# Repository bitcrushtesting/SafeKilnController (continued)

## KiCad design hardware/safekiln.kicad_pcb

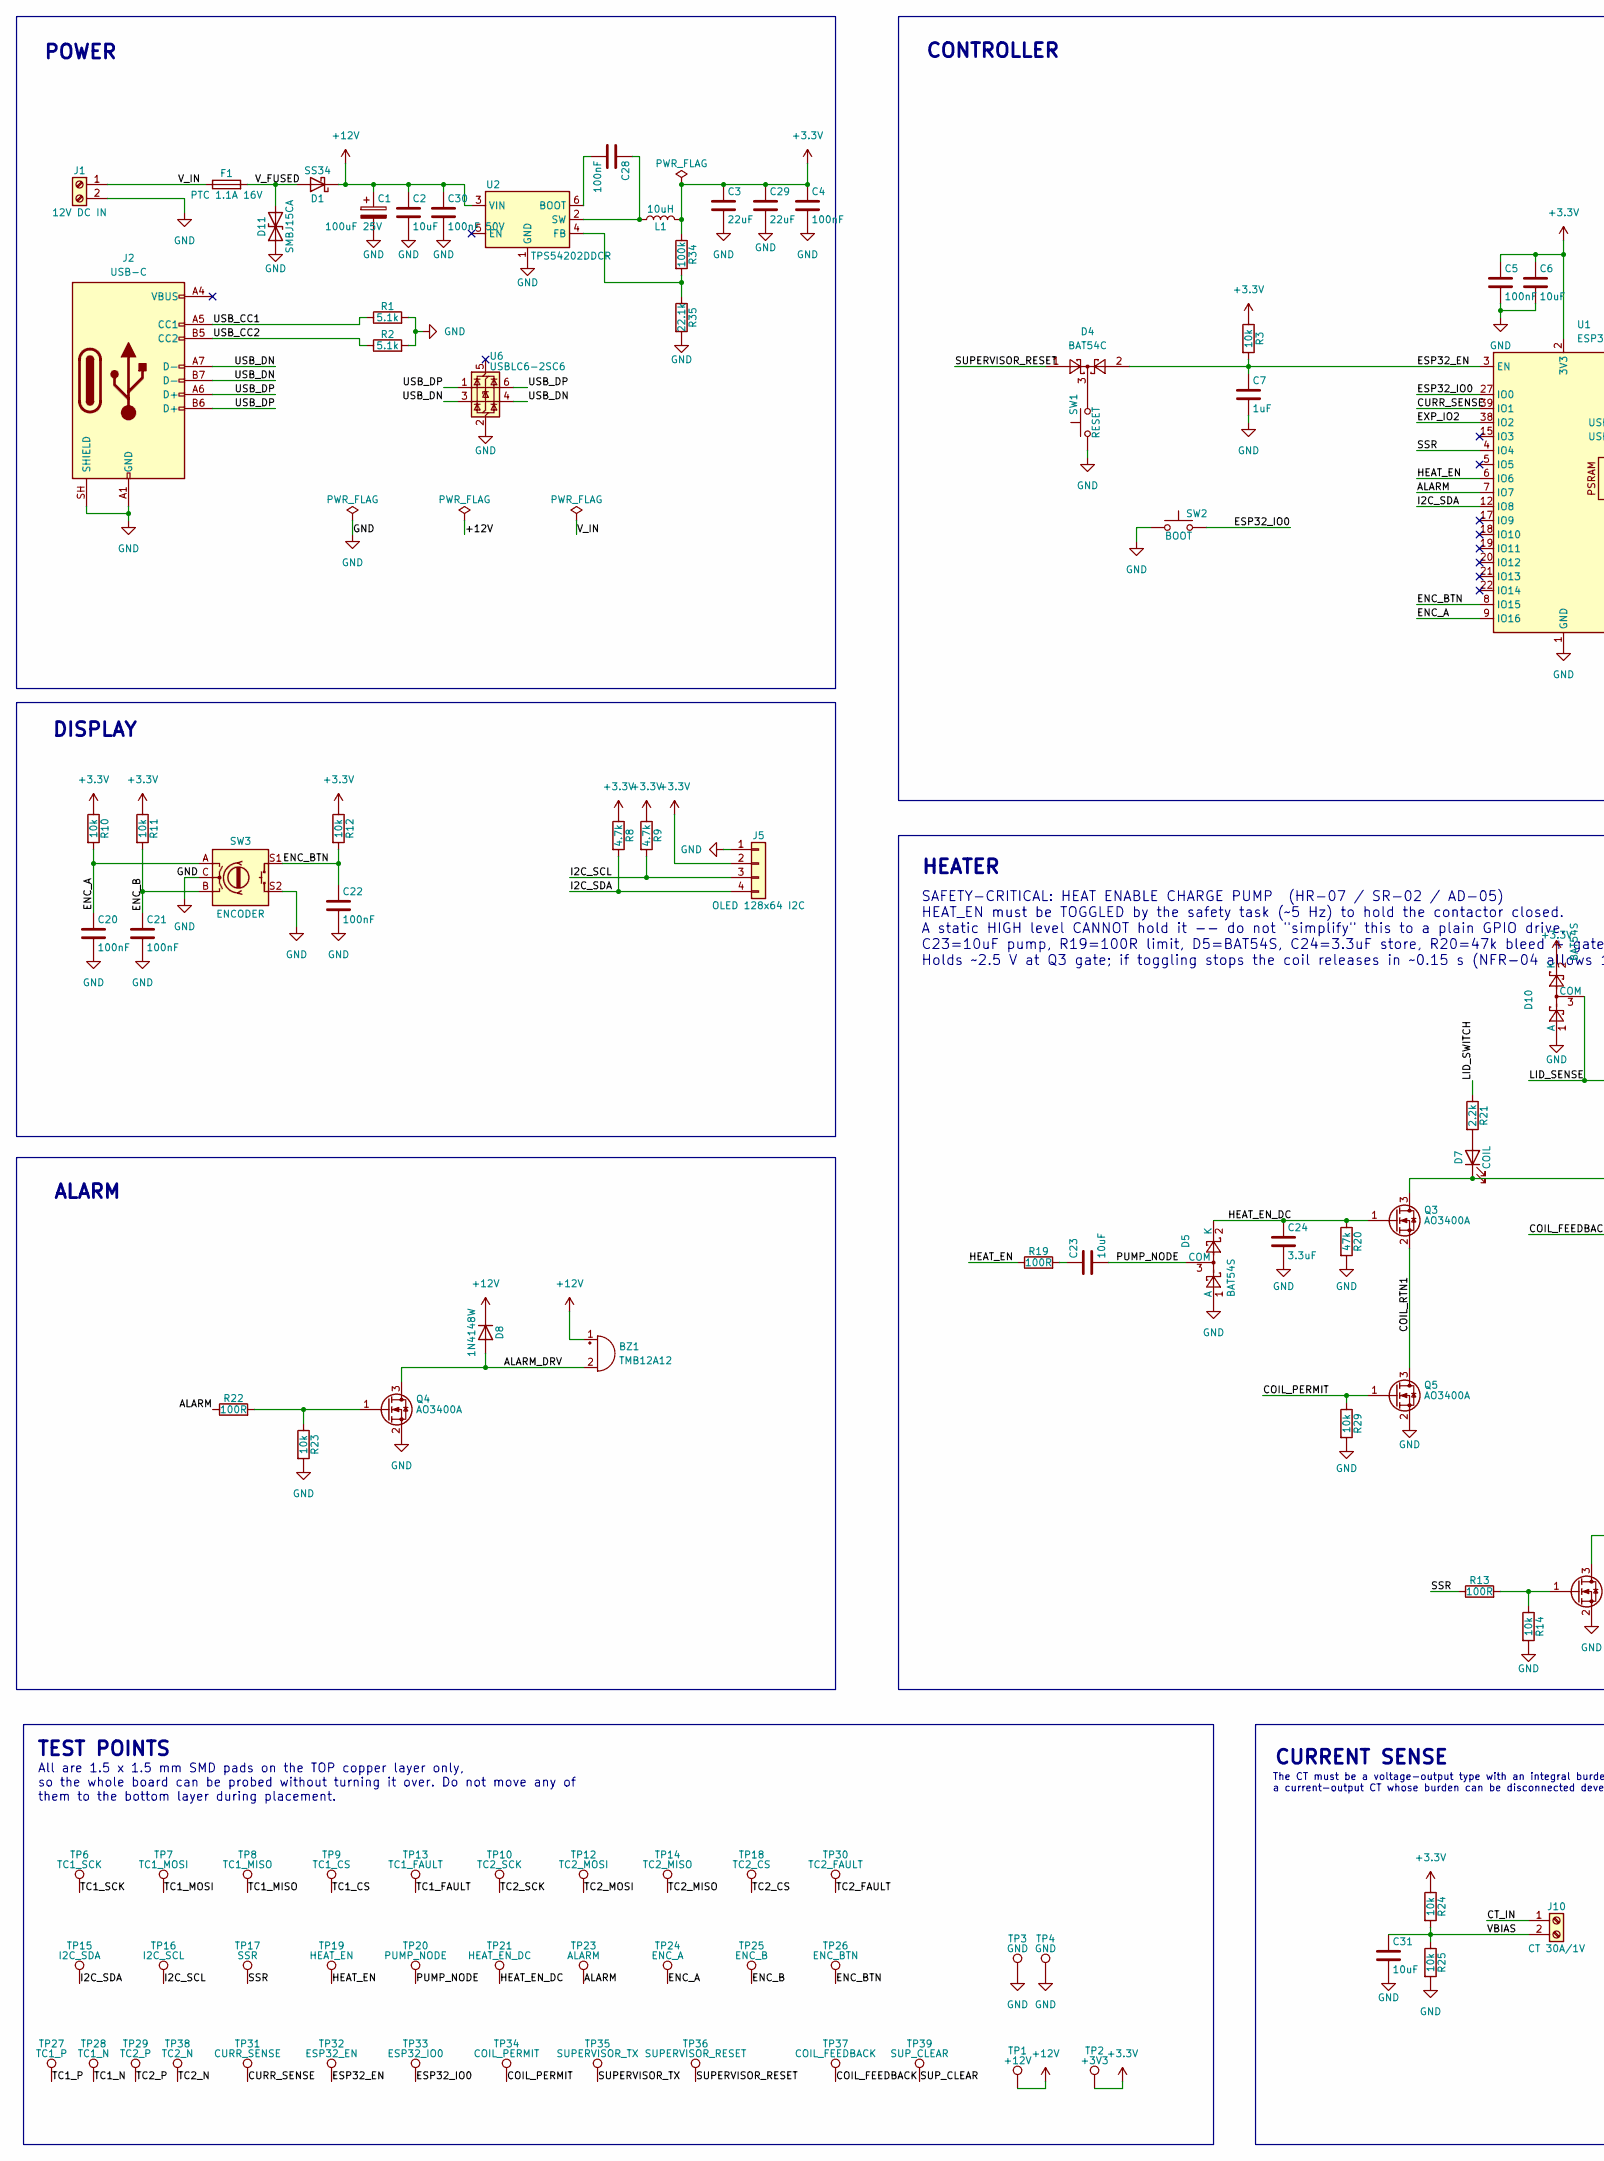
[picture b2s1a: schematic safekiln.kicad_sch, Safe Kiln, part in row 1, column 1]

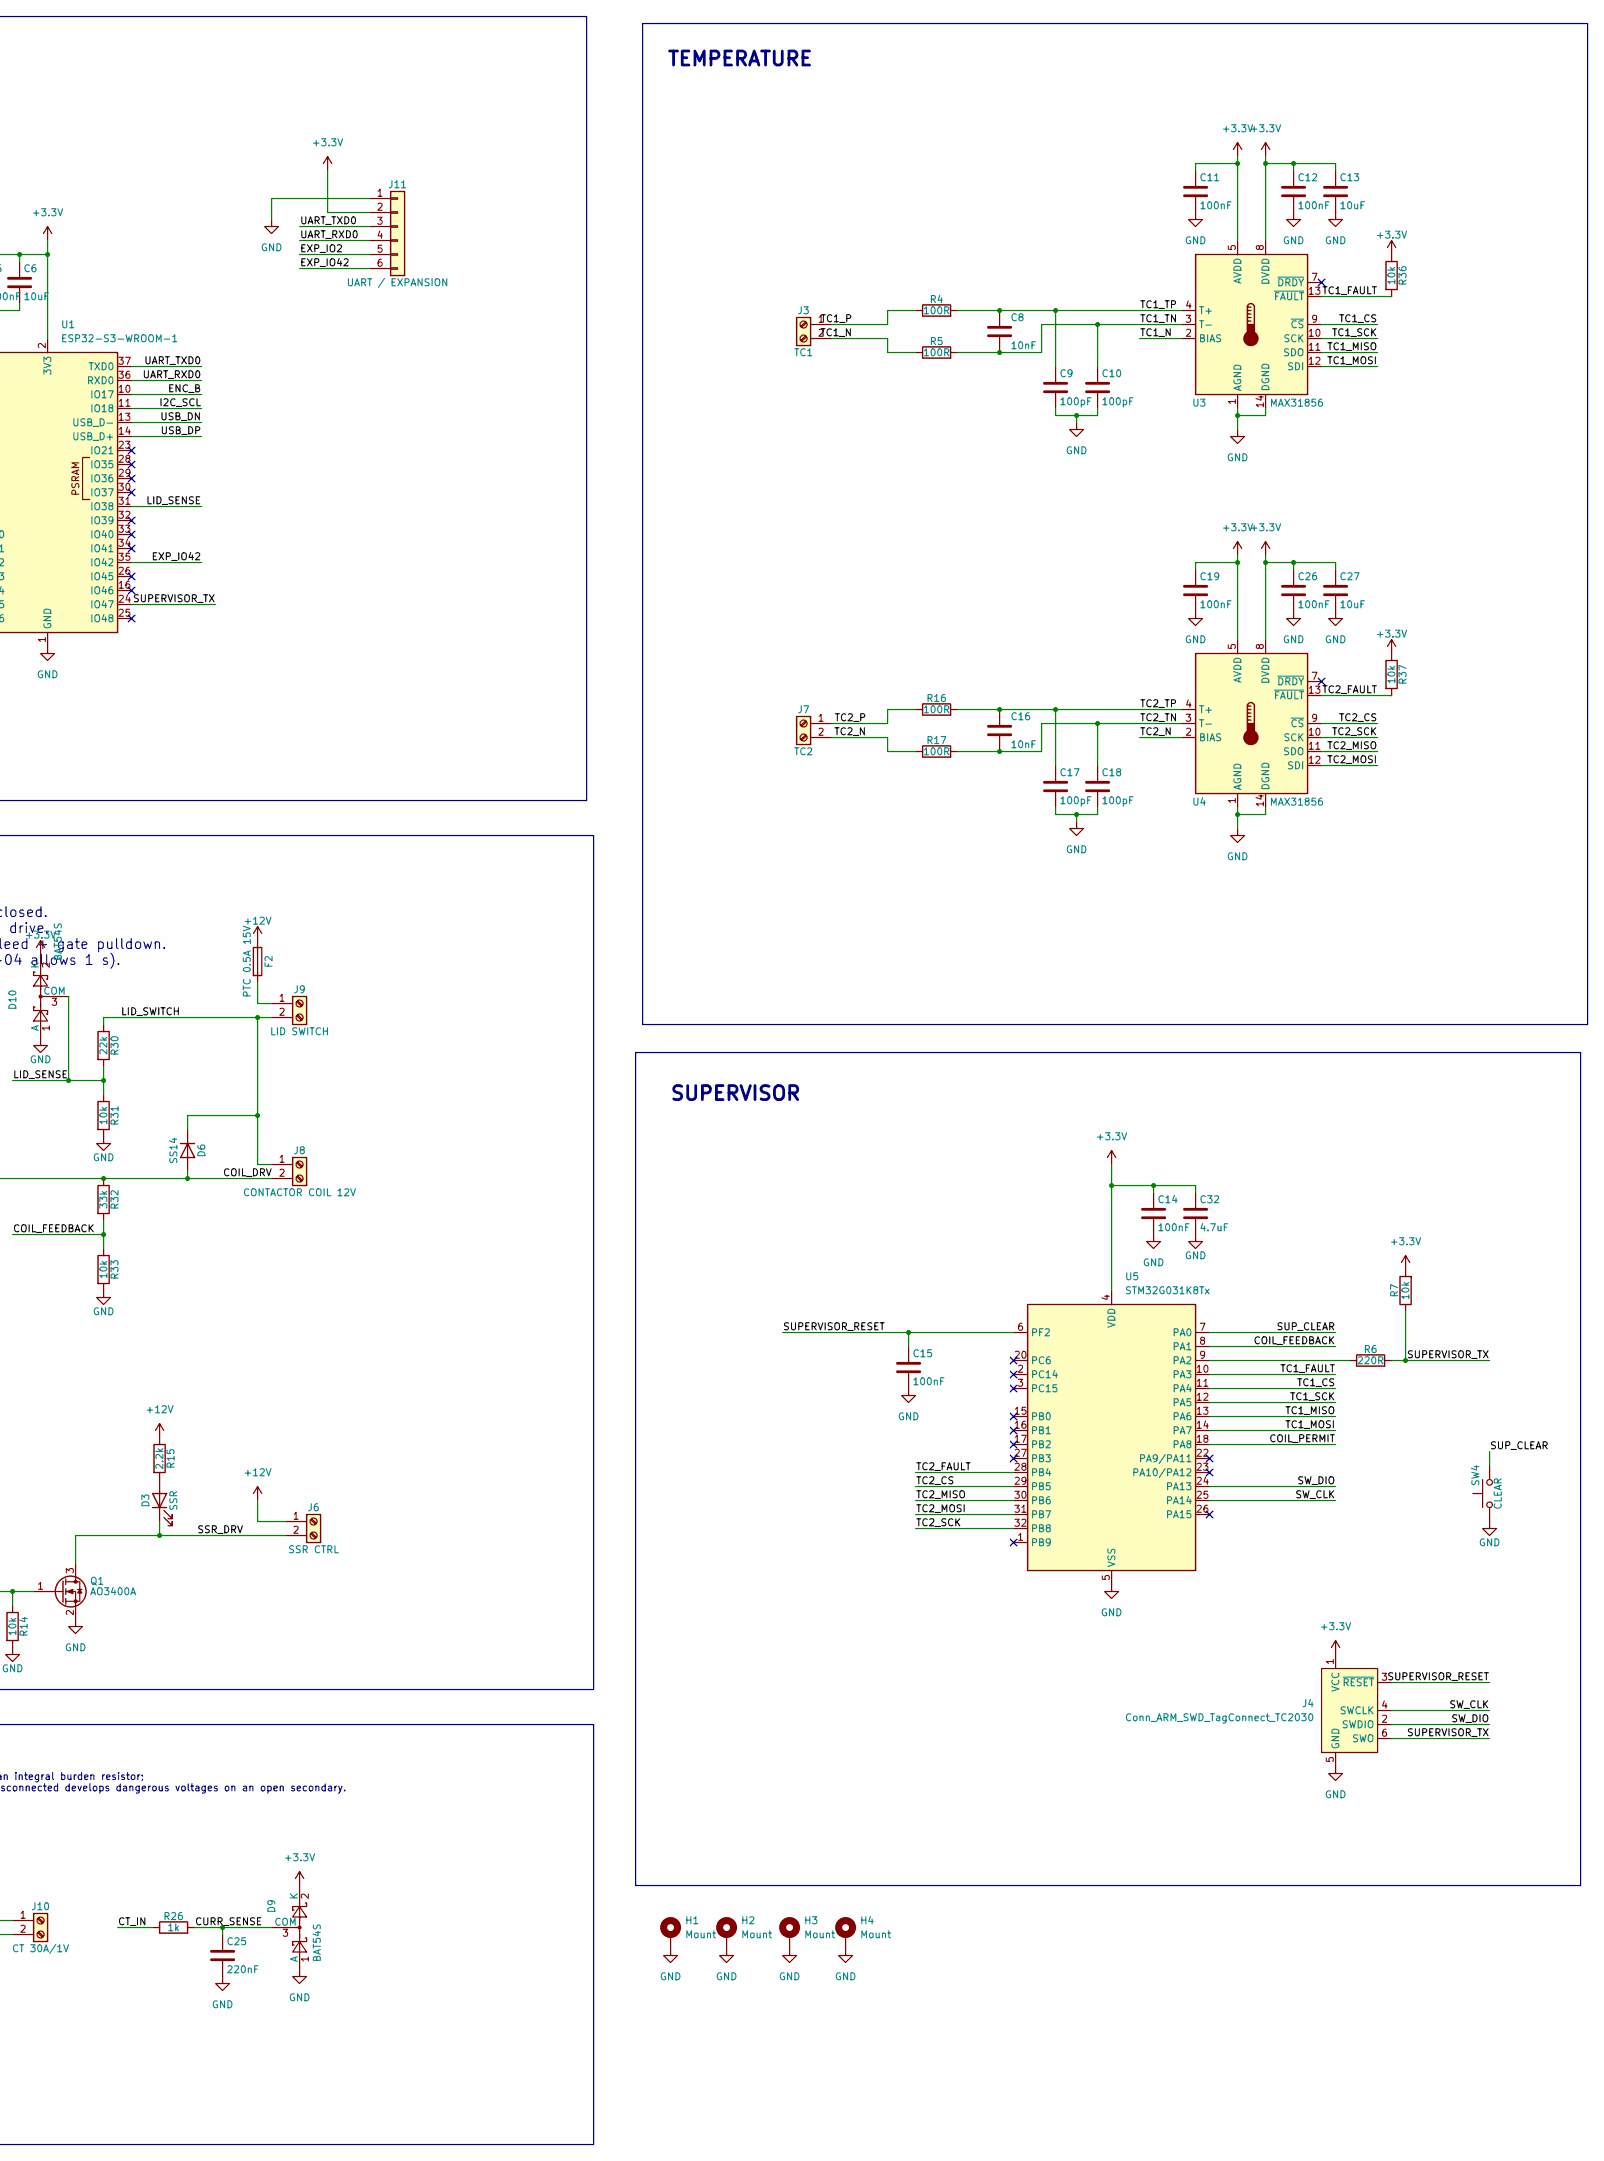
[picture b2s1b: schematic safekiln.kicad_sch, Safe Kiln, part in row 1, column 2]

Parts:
BZ1: TMB12A12; Buzzer_12x9.5RM7.6; LCSC C96079
C1: 100uF 25V; CP_Elec_6.3x7.7; LCSC C176675
C2, C6, C13, C23, C27, C31: 10uF; C_0805_2012Metric; LCSC C15850
C3, C29: 22uF; C_0805_2012Metric; LCSC C45783
C4, C5, C11, C12, C14, C15, C19, C20, C21, C22, C26, C28: 100nF; C_0402_1005Metric; LCSC C1525
C7: 1uF; C_0402_1005Metric; LCSC C52923
C8, C16: 10nF; C_0402_1005Metric; LCSC C15195
C9, C10, C17, C18: 100pF; C_0402_1005Metric; LCSC C26409
C24: 3.3uF; C_0805_2012Metric; LCSC C159781
C25: 220nF; C_0402_1005Metric; LCSC C16772
C30: 100nF 50V; C_0603_1608Metric; LCSC C14663
C32: 4.7uF; C_0603_1608Metric; LCSC C19666
D1: SS34; D_SMA; LCSC C8678
D3: SSR; LED_0603_1608Metric; LCSC C2286
D4: BAT54C; SOT-23; LCSC C37704
D5, D9, D10: BAT54S; SOT-23; LCSC C19726
D6: SS14; D_SMA; LCSC C2480
D7: COIL; LED_0603_1608Metric; LCSC C2286
D8: 1N4148W; D_SOD-123; LCSC C2099
D11: SMBJ15CA; D_SMB; LCSC C78410
F1: PTC 1.1A 16V; Fuse_1206_3216Metric; LCSC C7542961
F2: PTC 0.5A 15V; Fuse_1206_3216Metric; LCSC C151162
H1, H2, H3, H4: Mount; MountingHole_3.2mm_M3_ISO7380_Pad
J1: 12V DC IN; TerminalBlock_MaiXu_MX126-5.0-02P_1x02_P5.00mm; LCSC C474881
J2: USB-C; USB_C_Receptacle_HRO_TYPE-C-31-M-12; LCSC C165948
J3: TC1; TerminalBlock_MaiXu_MX126-5.0-02P_1x02_P5.00mm; LCSC C474881
J4: Conn_ARM_SWD_TagConnect_TC2030; Tag-Connect_TC2030-IDC-NL_2x03_P1.27mm_Vertical
J5: OLED 128x64 I2C; PinSocket_1x04_P2.54mm_Vertical
J6: SSR CTRL; TerminalBlock_MaiXu_MX126-5.0-02P_1x02_P5.00mm; LCSC C474881
J7: TC2; TerminalBlock_MaiXu_MX126-5.0-02P_1x02_P5.00mm; LCSC C474881
J8: CONTACTOR COIL 12V; TerminalBlock_MaiXu_MX126-5.0-02P_1x02_P5.00mm; LCSC C474881
J9: LID SWITCH; TerminalBlock_MaiXu_MX126-5.0-02P_1x02_P5.00mm; LCSC C474881
J10: CT 30A/1V; TerminalBlock_MaiXu_MX126-5.0-02P_1x02_P5.00mm; LCSC C474881
J11: UART / EXPANSION; PinHeader_1x06_P2.54mm_Vertical; LCSC C492405
L1: 10uH; L_Sunlord_SWPA5040S; LCSC C84608
Q1, Q3, Q4, Q5: AO3400A; SOT-23; LCSC C20917
R1, R2: 5.1k; R_0402_1005Metric; LCSC C25905
R3, R7, R10, R11, R12, R14, R23, R24, R25, R29, R31, R33, R36, R37: 10k; R_0402_1005Metric; LCSC C25744
R4, R5, R13, R16, R17, R19, R22: 100R; R_0402_1005Metric; LCSC C25076
R6: 220R; R_0402_1005Metric; LCSC C25091
R8, R9: 4.7k; R_0402_1005Metric; LCSC C25900
R15, R21: 2.2k; R_0603_1608Metric; LCSC C4190
R20: 47k; R_0402_1005Metric; LCSC C25792
R26: 1k; R_0402_1005Metric; LCSC C11702
R30: 22k; R_0402_1005Metric; LCSC C25768
R32: 33k; R_0402_1005Metric; LCSC C25779
R34: 100k; R_0402_1005Metric; LCSC C25741
R35: 22.1k; R_0402_1005Metric; LCSC C43473
SW1: RESET; SW_Push_1P1T_XKB_TS-1187A; LCSC C318884
SW2: BOOT; SW_Push_1P1T_XKB_TS-1187A; LCSC C318884
SW3: ENCODER; RotaryEncoder_Alps_EC11E-Switch_Vertical_H20mm; LCSC C7275025
SW4: CLEAR; SW_Push_1P1T_XKB_TS-1187A; LCSC C318884
TP1: +12V; TestPoint_Pad_1.5x1.5mm
TP2: +3V3; TestPoint_Pad_1.5x1.5mm
TP3, TP4: GND; TestPoint_Pad_1.5x1.5mm
TP6: TC1_SCK; TestPoint_Pad_1.5x1.5mm
TP7: TC1_MOSI; TestPoint_Pad_1.5x1.5mm
TP8: TC1_MISO; TestPoint_Pad_1.5x1.5mm
TP9: TC1_CS; TestPoint_Pad_1.5x1.5mm
TP10: TC2_SCK; TestPoint_Pad_1.5x1.5mm
TP12: TC2_MOSI; TestPoint_Pad_1.5x1.5mm
TP13: TC1_FAULT; TestPoint_Pad_1.5x1.5mm
TP14: TC2_MISO; TestPoint_Pad_1.5x1.5mm
TP15: I2C_SDA; TestPoint_Pad_1.5x1.5mm
TP16: I2C_SCL; TestPoint_Pad_1.5x1.5mm
TP17: SSR; TestPoint_Pad_1.5x1.5mm
TP18: TC2_CS; TestPoint_Pad_1.5x1.5mm
TP19: HEAT_EN; TestPoint_Pad_1.5x1.5mm
TP20: PUMP_NODE; TestPoint_Pad_1.5x1.5mm
TP21: HEAT_EN_DC; TestPoint_Pad_1.5x1.5mm
TP23: ALARM; TestPoint_Pad_1.5x1.5mm
TP24: ENC_A; TestPoint_Pad_1.5x1.5mm
TP25: ENC_B; TestPoint_Pad_1.5x1.5mm
TP26: ENC_BTN; TestPoint_Pad_1.5x1.5mm
TP27: TC1_P; TestPoint_Pad_1.5x1.5mm
TP28: TC1_N; TestPoint_Pad_1.5x1.5mm
TP29: TC2_P; TestPoint_Pad_1.5x1.5mm
TP30: TC2_FAULT; TestPoint_Pad_1.5x1.5mm
TP31: CURR_SENSE; TestPoint_Pad_1.5x1.5mm
TP32: ESP32_EN; TestPoint_Pad_1.5x1.5mm
TP33: ESP32_IO0; TestPoint_Pad_1.5x1.5mm
TP34: COIL_PERMIT; TestPoint_Pad_1.5x1.5mm
TP35: SUPERVISOR_TX; TestPoint_Pad_1.5x1.5mm
TP36: SUPERVISOR_RESET; TestPoint_Pad_1.5x1.5mm
TP37: COIL_FEEDBACK; TestPoint_Pad_1.5x1.5mm
TP38: TC2_N; TestPoint_Pad_1.5x1.5mm
TP39: SUP_CLEAR; TestPoint_Pad_1.5x1.5mm
U1: ESP32-S3-WROOM-1; LCSC C2913198
U2: TPS54202DDCR; SOT-23-6; LCSC C191884
U3, U4: MAX31856; TSSOP-14_4.4x5mm_P0.65mm; LCSC C2653162
U5: STM32G031K8Tx; LQFP-32_7x7mm_P0.8mm; LCSC C432203
U6: USBLC6-2SC6; SOT-23-6; LCSC C7519

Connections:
+3.3V: C3.1, C4.1, C5.1, C6.1, C11.1, C12.1, C13.1, C14.1, C19.1, C26.1, C27.1, C29.1, C32.1, D9.2 (K), D10.2 (K), J4.1 (VCC), J5.2, J11.2, L1.2, R3.1, R7.2, R8.1, R9.1, R10.1, R11.1, R12.1, R24.1, R34.1, R36.1, R37.1, TP2.1 (1_1), U1.2 (3V3), U3.5 (AVDD), U3.8 (DVDD), U4.5 (AVDD), U4.8 (DVDD), U5.4 (VDD)
+12V: BZ1.1 (+), C1.1, C2.1, C30.1, D1.1 (K), D8.1 (K), F2.1, J6.1, R15.1, TP1.1 (1_1), U2.3 (VIN)
/ALARM: R22.1, TP23.1 (1_1), U1.7 (IO7)
/ALARM_DRV: BZ1.2 (-), D8.2 (A), Q4.3 (D)
/COIL_DRV: D6.2 (A), D7.1 (K), J8.2, Q3.3 (D), R32.1
/COIL_FEEDBACK: R32.2, R33.1, TP37.1 (1_1), U5.8 (PA1)
/COIL_PERMIT: Q5.1 (G), R29.1, TP34.1 (1_1), U5.18 (PA8)
/COIL_RTN1: Q3.2 (S), Q5.3 (D)
/CT_IN: J10.1, R26.1
/CURR_SENSE: C25.1, D9.3 (COM), R26.2, TP31.1 (1_1), U1.39 (IO1)
/ENC_A: C20.1, R10.2, SW3.A, TP24.1 (1_1), U1.9 (IO16)
/ENC_B: C21.1, R11.2, SW3.B, TP25.1 (1_1), U1.10 (IO17)
/ENC_BTN: C22.1, R12.2, SW3.S1, TP26.1 (1_1), U1.8 (IO15)
/ESP32_EN: C7.1, D4.2, R3.2, TP32.1 (1_1), U1.3 (EN)
/ESP32_IO0: SW2.2, TP33.1 (1_1), U1.27 (IO0)
/EXP_IO2: J11.5, U1.38 (IO2)
/EXP_IO42: J11.6, U1.35 (IO42)
/HEAT_EN: R19.1, TP19.1 (1_1), U1.6 (IO6)
/HEAT_EN_DC: C24.1, D5.2 (K), Q3.1 (G), R20.1, TP21.1 (1_1)
/I2C_SCL: J5.3, R9.2, TP16.1 (1_1), U1.11 (IO18)
/I2C_SDA: J5.4, R8.2, TP15.1 (1_1), U1.12 (IO8)
/LID_SENSE: D10.3 (COM), R30.2, R31.1, U1.31 (IO38)
/LID_SWITCH: D6.1 (K), J8.1, J9.2, R21.1, R30.1
/PUMP_NODE: C23.2, D5.3 (COM), TP20.1 (1_1)
/SSR: R13.1, TP17.1 (1_1), U1.4 (IO4)
/SSR_DRV: D3.1 (K), J6.2, Q1.3 (D)
/SUPERVISOR_RESET: C15.1, D4.1, J4.3 (~RESET), TP36.1 (1_1), U5.6 (PF2)
/SUPERVISOR_TX: J4.6 (SWO), R6.2, R7.1, TP35.1 (1_1), U1.24 (IO47)
/SUP_CLEAR: SW4.2, TP39.1 (1_1), U5.7 (PA0)
/SW_CLK: J4.4 (SWCLK), U5.25 (PA14)
/SW_DIO: J4.2 (SWDIO), U5.24 (PA13)
/TC1_CS: TP9.1 (1_1), U3.9 (~CS), U5.11 (PA4)
/TC1_FAULT: R36.2, TP13.1 (1_1), U3.13 (~FAULT), U5.10 (PA3)
/TC1_MISO: TP8.1 (1_1), U3.11 (SDO), U5.13 (PA6)
/TC1_MOSI: TP7.1 (1_1), U3.12 (SDI), U5.14 (PA7)
/TC1_N: J3.2, R5.1, TP28.1 (1_1), U3.2 (BIAS)
/TC1_P: J3.1, R4.1, TP27.1 (1_1)
/TC1_SCK: TP6.1 (1_1), U3.10 (SCK), U5.12 (PA5)
/TC1_TN: C8.2, C10.1, R5.2, U3.3 (T-)
/TC1_TP: C8.1, C9.1, R4.2, U3.4 (T+)
/TC2_CS: TP18.1 (1_1), U4.9 (~CS), U5.29 (PB5)
/TC2_FAULT: R37.2, TP30.1 (1_1), U4.13 (~FAULT), U5.28 (PB4)
/TC2_MISO: TP14.1 (1_1), U4.11 (SDO), U5.30 (PB6)
/TC2_MOSI: TP12.1 (1_1), U4.12 (SDI), U5.31 (PB7)
/TC2_N: J7.2, R17.1, TP38.1 (1_1), U4.2 (BIAS)
/TC2_P: J7.1, R16.1, TP29.1 (1_1)
/TC2_SCK: TP10.1 (1_1), U4.10 (SCK), U5.32 (PB8)
/TC2_TN: C16.2, C18.1, R17.2, U4.3 (T-)
/TC2_TP: C16.1, C17.1, R16.2, U4.4 (T+)
/UART_RXD0: J11.4, U1.36 (RXD0)
/UART_TXD0: J11.3, U1.37 (TXD0)
/USB_CC1: J2.A5 (CC1), R1.1
/USB_CC2: J2.B5 (CC2), R2.1
/USB_DN: J2.A7 (D-), J2.B7 (D-), U1.13 (USB_D-), U6.3 (I/O2), U6.4 (I/O2)
/USB_DP: J2.A6 (D+), J2.B6 (D+), U1.14 (USB_D+), U6.1 (I/O1), U6.6 (I/O1)
/VBIAS: C31.1, J10.2, R24.2, R25.1
/V_FUSED: D1.2 (A), D11.2 (A2), F1.2
/V_IN: F1.1, J1.1
GND: C1.2, C2.2, C3.2, C4.2, C5.2, C6.2, C7.2, C9.2, C10.2, C11.2, C12.2, C13.2, C14.2, C15.2, C17.2, C18.2, C19.2, C20.2, C21.2, C22.2, C24.2, C25.2, C26.2, C27.2, C29.2, C30.2, C31.2, C32.2, D5.1 (A), D9.1 (A), D10.1 (A), D11.1 (A1), H1.1 (1_1), H2.1 (1_1), H3.1 (1_1), H4.1 (1_1), J1.2, J2.A1 (GND), J2.A12 (GND), J2.B1 (GND), J2.B12 (GND), J2.SH (SHIELD), J4.5 (GND), J5.1, J11.1, Q1.2 (S), Q4.2 (S), Q5.2 (S), R1.2, R2.2, R14.2, R20.2, R23.2, R25.2, R29.2, R31.2, R33.2, R35.2, SW1.1, SW2.1, SW3.C, SW3.S2, SW4.1, TP3.1 (1_1), TP4.1 (1_1), U1.1 (GND), U1.40 (GND), U1.41 (GND), U2.1 (GND), U3.1 (AGND), U3.14 (DGND), U4.1 (AGND), U4.14 (DGND), U5.5 (VSS), U6.2 (GND)
unnamed: C23.1, R19.2
unnamed: D3.2 (A), R15.2
unnamed: D4.3, SW1.2
unnamed: D7.2 (A), R21.2
unnamed: F2.2, J9.1
unnamed: Q1.1 (G), R13.2, R14.1
unnamed: Q4.1 (G), R22.2, R23.1
unnamed: C28.2, U2.6 (BOOT)
unnamed: R34.2, R35.1, U2.4 (FB)
unnamed: C28.1, L1.1, U2.2 (SW)
unnamed: R6.1, U5.9 (PA2)

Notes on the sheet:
The CT must be a voltage-output type with an integral burden resistor; a current-output CT whose burden can be disconnected develops dangerous voltages on an open secondary.
TEMPERATURE
DISPLAY
TEST POINTS
SAFETY-CRITICAL: HEAT ENABLE CHARGE PUMP (HR-07 / SR-02 / AD-05) HEAT_EN must be TOGGLED by the safety task (~5 Hz) to hold the contactor closed. A static HIGH level CANNOT hold it -- do not "simplify" this to a plain GPIO drive. C23=10uF pump, R19=100R limit, D5=BAT54S, C24=3.3uF store, R20=47k bl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
CURRENT SENSE
POWER
ALARM
HEATER
CONTROLLER
SUPERVISOR
All are 1.5 x 1.5 mm SMD pads on the TOP copper layer only, so the whole board can be probed without turning it over. Do not move any of them to the bottom layer during placement.

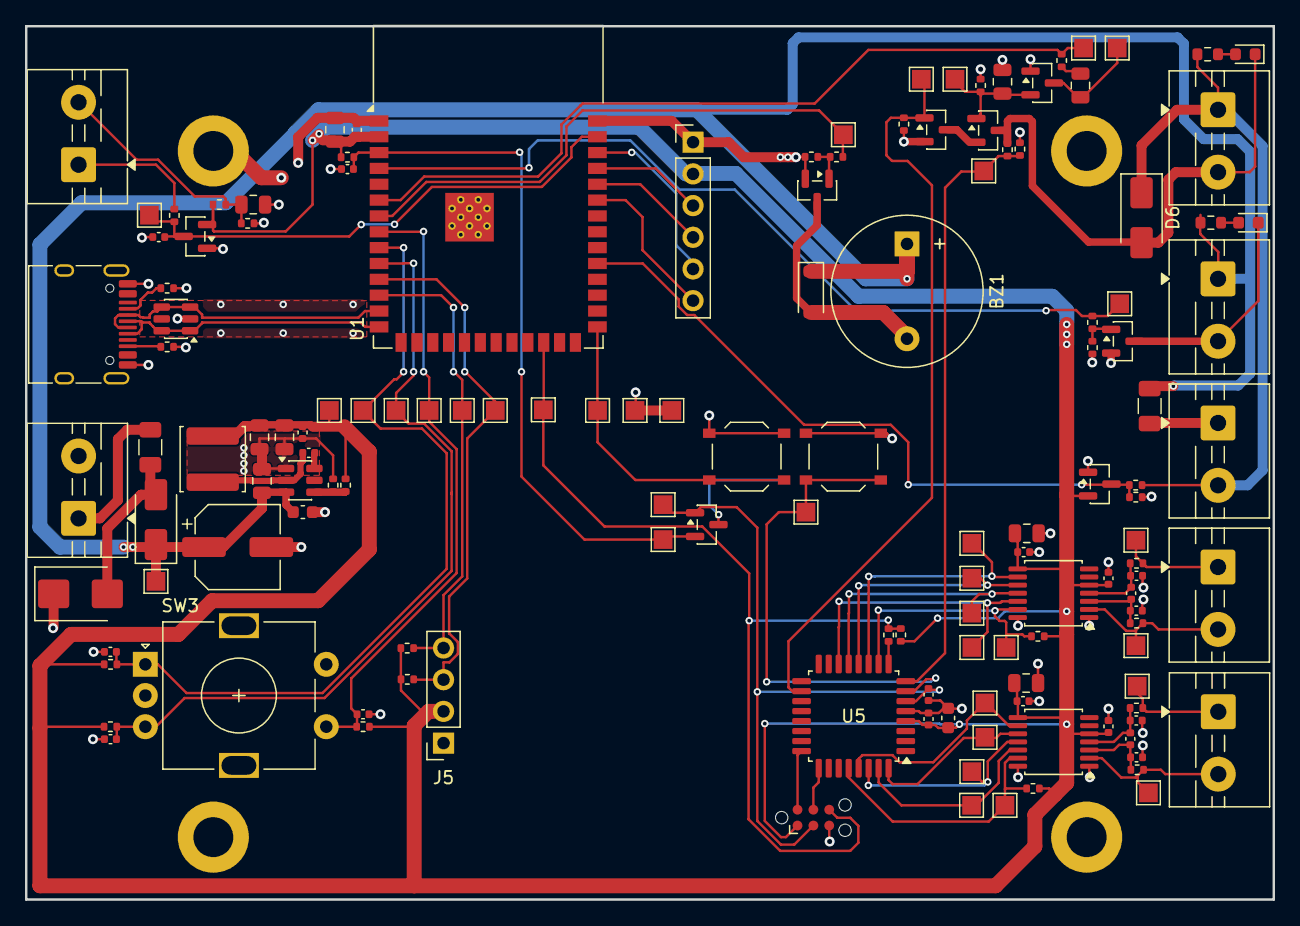
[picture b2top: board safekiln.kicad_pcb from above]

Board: 2 copper layers, 100.0 x 70.0 mm, 145 parts (1 on the bottom side), 70 nets.

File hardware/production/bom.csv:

Designator,Footprint,Quantity,Value,LCSC Part #
BZ1,Buzzer_12x9.5RM7.6,1,TMB12A12,C96079
C1,CP_Elec_6.3x7.7,1,100uF 25V,C176675
"C10, C17, C18, C9",0402,4,100pF,C26409
"C11, C12, C14, C15, C19, C20, C21, C22, C26, C28, C4, C5",0402,12,100nF,C1525
"C13, C2, C23, C27, C31, C6",0805,6,10uF,C15850
"C16, C8",0402,2,10nF,C15195
C24,0805,1,3.3uF,C159781
C25,0402,1,220nF,C16772
"C29, C3",0805,2,22uF,C45783
C30,0603,1,100nF 50V,C14663
C32,0603,1,4.7uF,C19666
C7,0402,1,1uF,C52923
D1,D_SMA,1,SS34,C8678
"D10, D5, D9",SOT-23,3,BAT54S,C19726
D11,D_SMB,1,SMBJ15CA,C78410
D3,0603,1,SSR,C2286
D4,SOT-23,1,BAT54C,C37704
D6,D_SMA,1,SS14,C2480
D7,0603,1,COIL,C2286
D8,D_SOD-123,1,1N4148W,C2099
F1,1206,1,PTC 1.1A 16V,C7542961
F2,1206,1,PTC 0.5A 15V,C151162
J1,TerminalBlock_MaiXu_MX126-5.0-02P_1x02_P5.00mm,1,12V DC IN,C474881
J10,TerminalBlock_MaiXu_MX126-5.0-02P_1x02_P5.00mm,1,CT 30A/1V,C474881
J2,USB_C_Receptacle_HRO_TYPE-C-31-M-12,1,USB-C,C165948
J3,TerminalBlock_MaiXu_MX126-5.0-02P_1x02_P5.00mm,1,TC1,C474881
J6,TerminalBlock_MaiXu_MX126-5.0-02P_1x02_P5.00mm,1,SSR CTRL,C474881
J7,TerminalBlock_MaiXu_MX126-5.0-02P_1x02_P5.00mm,1,TC2,C474881
J8,TerminalBlock_MaiXu_MX126-5.0-02P_1x02_P5.00mm,1,CONTACTOR COIL 12V,C474881
J9,TerminalBlock_MaiXu_MX126-5.0-02P_1x02_P5.00mm,1,LID SWITCH,C474881
L1,L_Sunlord_SWPA5040S,1,10uH,C84608
"Q1, Q3, Q4, Q5",SOT-23,4,AO3400A,C20917
"R1, R2",0402,2,5.1k,C25905
"R10, R11, R12, R14, R23, R24, R25, R29, R3, R31, R33, R36, R37, R7",0402,14,10k,C25744
"R13, R16, R17, R19, R22, R4, R5",0402,7,100R,C25076
"R15, R21",0603,2,2.2k,C4190
R20,0402,1,47k,C25792
R26,0402,1,1k,C11702
R30,0402,1,22k,C25768
R32,0402,1,33k,C25779
R34,0402,1,100k,C25741
R35,0402,1,22.1k,C43473
R6,0402,1,220R,C25091
"R8, R9",0402,2,4.7k,C25900
SW1,SW_Push_1P1T_XKB_TS-1187A,1,RESET,C318884
SW2,SW_Push_1P1T_XKB_TS-1187A,1,BOOT,C318884
SW3,RotaryEncoder_Alps_EC11E-Switch_Vertical_H20mm,1,ENCODER,C7275025
SW4,SW_Push_1P1T_XKB_TS-1187A,1,CLEAR,C318884
U2,SOT-23-6,1,TPS54202DDCR,C191884
"U3, U4",TSSOP-14_4.4x5mm_P0.65mm,2,MAX31856,C2653162
U5,LQFP-32_7x7mm_P0.8mm,1,STM32G031K8Tx,C432203
U6,SOT-23-6,1,USBLC6-2SC6,C7519

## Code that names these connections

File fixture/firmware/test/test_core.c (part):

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  check(fx_uart_count == 1, "the config declares 1 uart buses");
  check(fx_i2c_count == 1, "the config declares 1 i2c buses");
  check(fx_spi_count == 1, "the config declares 1 spi buses");
  check(strcmp(fx_gpio[0].name, "tc1_cs") == 0 && fx_gpio[0].pin == 6, "tc1_cs is on GPIO6");
  check(strcmp(fx_gpio[1].name, "tc1_drdy") == 0 && fx_gpio[1].pin == 7, "tc1_drdy is on GPIO7");
  check(strcmp(fx_gpio[2].name, "tc1_fault") == 0 && fx_gpio[2].pin == 8, "tc1_fault is on GPIO8");
  check(strcmp(fx_gpio[3].name, "ssr1") == 0 && fx_gpio[3].pin == 9, "ssr1 is on GPIO9");
  check(strcmp(fx_gpio[4].name, "heat_en") == 0 && fx_gpio[4].pin == 10, "heat_en is on GPIO10");
  check(strcmp(fx_gpio[5].name, "pump_node") == 0 && fx_gpio[5].pin == 11, "pump_node is on GPIO11");
  check(strcmp(fx_gpio[6].name, "heat_en_dc") == 0 && fx_gpio[6].pin == 12, "heat_en_dc is on GPIO12");
  check(strcmp(fx_gpio[7].name, "coil_drv") == 0 && fx_gpio[7].pin == 13, "coil_drv is on GPIO13");
  check(strcmp(fx_gpio[8].name, "alarm") == 0 && fx_gpio[8].pin == 14, "alarm is on GPIO14");
  check(strcmp(fx_gpio[9].name, "enc_a") == 0 && fx_gpio[9].pin == 15, "enc_a is on GPIO15");
  check(strcmp(fx_gpio[10].name, "enc_b") == 0 && fx_gpio[10].pin == 16, "enc_b is on GPIO16");
  check(strcmp(fx_gpio[11].name, "enc_btn") == 0 && fx_gpio[11].pin == 17, "enc_btn is on GPIO17");
  check(strcmp(fx_gpio[12].name, "tc1_p") == 0 && fx_gpio[12].pin == 18, "tc1_p is on GPIO18");
  check(strcmp(fx_gpio[13].name, "tc1_n") == 0 && fx_gpio[13].pin == 19, "tc1_n is on GPIO19");
  check(strcmp(fx_gpio[14].name, "curr_sense") == 0 && fx_gpio[14].pin == 20, "curr_sense is on GPIO20");
  check(strcmp(fx_gpio[15].name, "esp32_en") == 0 && fx_gpio[15].pin == 21, "esp32_en is on GPIO21");
  check(strcmp(fx_gpio[16].name, "esp32_io0") == 0 && fx_gpio[16].pin == 22, "esp32_io0 is on GPIO22");
  check(strcmp(fx_gpio[17].name, "coil_permit") == 0 && fx_gpio[17].pin == 23, "coil_permit is on GPIO23");
  check(strcmp(fx_gpio[18].name, "supervisor_reset") == 0 && fx_gpio[18].pin == 24, "supervisor_reset is on GPIO24");
  check(strcmp(fx_adc[0].name, "ch_5v") == 0 && fx_adc[0].adc == 0, "ch_5v reads ADC0");
  check(strcmp(fx_adc[1].name, "ch_3_3v") == 0 && fx_adc[1].adc == 1, "ch_3_3v reads ADC1");
  check(strcmp(fx_uart[0].name, "supervisor_uart") == 0 && fx_uart[0].index == 0, "supervisor_uart is uart0");
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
